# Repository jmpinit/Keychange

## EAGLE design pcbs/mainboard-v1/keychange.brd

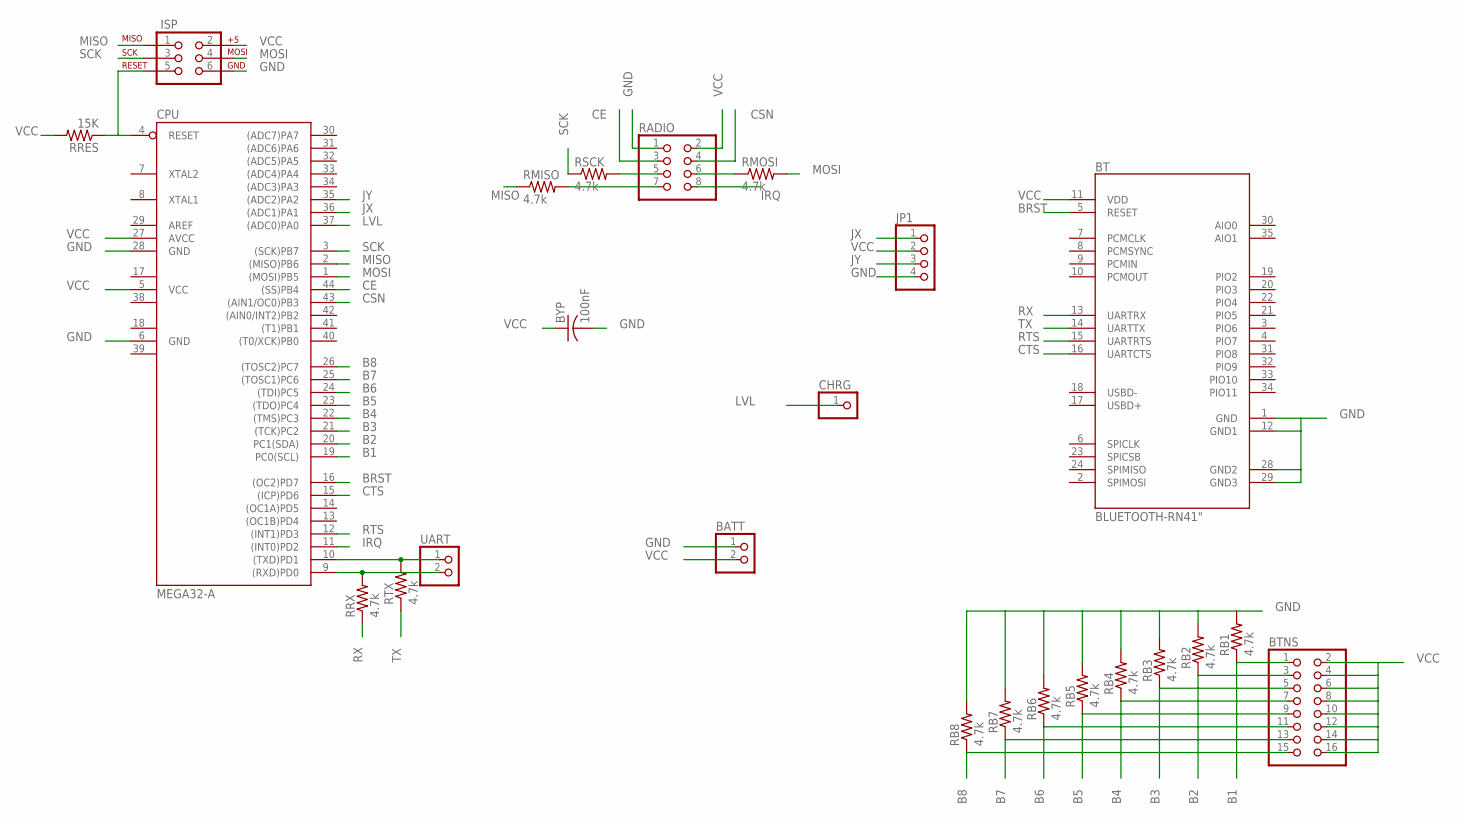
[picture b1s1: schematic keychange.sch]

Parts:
BATT: PINHD-1X2; 1X02
BT: BLUETOOTH-RN41"; RN41
BTNS: PINHD-2X8; 2X08
BYP: 100nF; C0603
CHRG: PINHD-1X1; 1X01
CPU: MEGA32-A; TQFP44
ISP: AVR_SPI_PRG_62X3_LOCK; 2X3_LOCK
JP1: PINHD-1X4; 1X04
RADIO: PINHD-2X4; 2X04
RB1, RB2, RB3, RB4, RB5, RB6, RB7, RB8: 4.7k; R0603
RMISO: 4.7k; R0603
RMOSI: 4.7k; R0603
RRES: 15K; R0603
RRX: 4.7k; R0603
RSCK: 4.7k; R0603
RTX: 4.7k; R0603
UART: PINHD-1X2; 1X02

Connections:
B1: BTNS.1, CPU.19 (PC0(SCL)), RB1.1
B2: BTNS.3, CPU.20 (PC1(SDA)), RB2.1
B3: BTNS.5, CPU.21 ((TCK)PC2), RB3.1
B4: BTNS.7, CPU.22 ((TMS)PC3), RB4.1
B5: BTNS.9, CPU.23 ((TDO)PC4), RB5.1
B6: BTNS.11, CPU.24 ((TDI)PC5), RB6.1
B7: BTNS.13, CPU.25 ((TOSC1)PC6), RB7.1
B8: BTNS.15, CPU.26 ((TOSC2)PC7), RB8.1
BRST: BT.5 (RESET), CPU.16 ((OC2)PD7)
CE: CPU.44 ((SS)PB4), RADIO.3
CSN: CPU.43 ((AIN1/OC0)PB3), RADIO.4
CTS: BT.16 (UARTCTS), CPU.15 ((ICP)PD6)
GND: BATT.1, BT.1 (GND), BT.12 (GND1), BT.28 (GND2), BT.29 (GND3), BYP.2, CPU.6 (GND), CPU.28 (GND), ISP.6, JP1.4, RADIO.1, RB1.2, RB2.2, RB3.2, RB4.2, RB5.2, RB6.2, RB7.2, RB8.2
GND1: CPU.18 (GND1)
GND2: CPU.39 (GND2)
IRQ: CPU.11 ((INT0)PD2), RADIO.8
JX: CPU.36 ((ADC1)PA1), JP1.1
JY: CPU.35 ((ADC2)PA2), JP1.3
LVL: CHRG.1, CPU.37 ((ADC0)PA0)
MISO: CPU.2 ((MISO)PB6), ISP.1, RMISO.1
MOSI: CPU.1 ((MOSI)PB5), ISP.4, RMOSI.2
unnamed: RADIO.5, RSCK.2
unnamed: RADIO.6, RMOSI.1
unnamed: CPU.4 (RESET), ISP.5, RRES.1
unnamed: CPU.10 ((TXD)PD1), RTX.2, UART.1
unnamed: CPU.9 ((RXD)PD0), RRX.2, UART.2
unnamed: RADIO.7, RMISO.2
RTS: BT.15 (UARTRTS), CPU.12 ((INT1)PD3)
RX: BT.13 (UARTRX), RRX.1
SCK: CPU.3 ((SCK)PB7), ISP.3, RSCK.1
TX: BT.14 (UARTTX), RTX.1
VCC: BATT.2, BT.11 (VDD), BTNS.2, BTNS.4, BTNS.6, BTNS.8, BTNS.10, BTNS.12, BTNS.14, BTNS.16, BYP.1, CPU.5 (VCC), CPU.27 (AVCC), ISP.2, JP1.2, RADIO.2, RRES.2
VCC1: CPU.17 (VCC1)
VCC2: CPU.38 (VCC2)

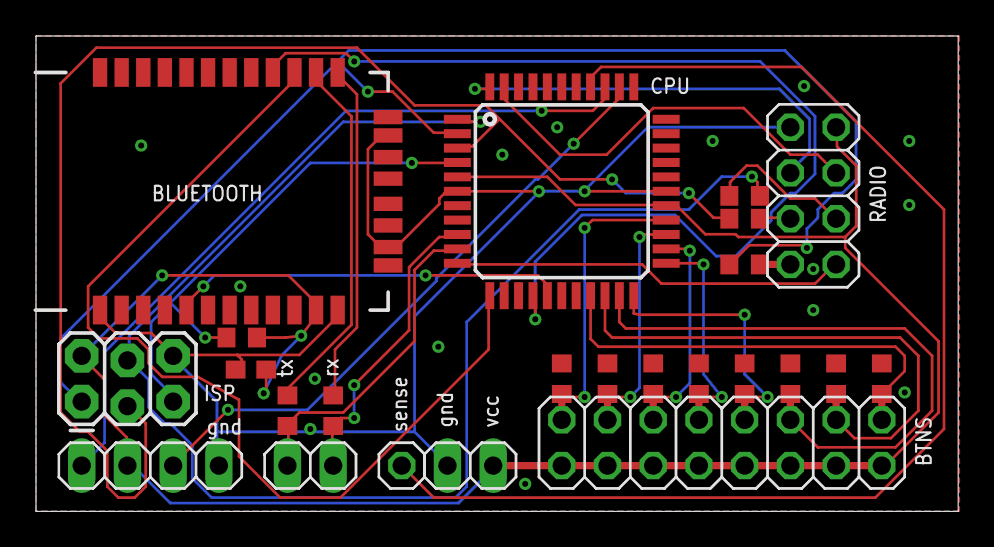
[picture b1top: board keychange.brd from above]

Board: 2 copper layers, 51.2 x 26.4 mm, 24 parts (0 on the bottom side), 30 nets.

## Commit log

2014-10-27 Able to type abcde with debouncing.
2014-10-29 Key reading factored into separate function.
2014-10-30 Measure and send time to press 2 chosen keys in order.
    * One byte command selects 2 keys. First key in lower nibble and second
    in upper.
    * Time is returned as milliseconds in the form of 4 bytes (a long).
2014-10-30 Read time between keypresses over serial.
2014-10-30 Removing boolean hacks fixes missing top 2 keys.
2014-10-30 Present graphic prompt and save data to csv file.
2014-10-30 Ignore Processing and Arduino sketch property files.
2014-10-30 Ignore data files.
2014-10-30 Fix intermittent failure of serial sync.
2014-10-30 Graph data files on key sequence timing.
2014-11-25 Special place for prototype work.
2014-11-25 Laser-cut grip shape studies.
2014-11-25 First version of mainboard. Older version with wrong SPI wiring sent to fab.
2014-12-06 Ignoring compilation files.
2014-12-06 Basic test assigning the first letters of the alphabet to the buttons.
2014-12-10 Debouncing the basic test.
2015-07-14 Arpeggios and chords.
2015-07-14 Function keys for Eagle.
2015-07-15 Reorganized & unit tests.
2015-07-15 Guard less likely to conflict.
2015-07-15 Fix type declaration.
2015-07-15 Serial fixes.
2015-07-15 Use correct signature.
2015-07-15 SPP mode debugging.

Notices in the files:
parts and their libraries:
SparkFun-Connectors: Licensing: Creative Commons ShareAlike 4.0 International - https://creativecommons.org/licenses/by-sa/4.0
